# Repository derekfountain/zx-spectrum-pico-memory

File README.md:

# zx-spectrum-pico-memory

## A Microcontroller-based Lower Memory Implementation for the ZX Spectrum

This project replaces the 16K of lower memory in the ZX Spectrum with a Raspberry Pi Pico2. The RP2350
microcontoller on the Pico is programmed to emulate the original MK4116 DRAM ICs, and responds to reads
and writes from the Z80 CPU and the Spectrum's ULA support chip in the same way the original memory
does. It's not a cycle-perfect implementation, as I'll discuss, and to be honest it's of limited
practical use in this age of cheap SRAM based memory modules. But it was an interesting project, both
from a ZX point of view, and that of pushing the Pico to its limits.

### History

The original work on this project was done by myself and Andrew Menadue in 2022. Andrew designed the board
for the RP2040-based Raspberrry Pi Pico, and that work is still in
<a href="https://github.com/blackjetrock/zx-spectrum-pico-memory">his repository</a>. In late 2022 it
defeated us, the RP2040 just couldn't go fast enough to match 150ns silicon. I picked the project up
again in summer 2025 and had another look at it. Still unable to get it working, I changed it to use
the RP2350-based Pico2, and, that being a faster and more easily overclockable device, was able to
do the task. Just.

## The Technical Challenge

The MK4116 DRAM ICs in the ZX Spectrum provide the machine's lower 16K of RAM (memory locations 0x4000 to
0x7FFF inclusive). This memory area contains the memory used to create the Spectrum's memory mapped
video display (memory area 0x4000 to 0x5AFF inclusive). As such the 16K memory area is used by both the
Z80 CPU and the ULA support chip which is responsible for generating a video display from the memory
area.

The MK4116s used in the Spectrum are rated at 150ns, meaning a single read or write operation will
complete inside 150ns. Although the Z80 doesn't drive the DRAM ICs at their fastest speed, the ULA does.
This is because the ULA was tuned to generate the video image as quickly as possible, thereby not
slowing down the rest of the ZX Spectrum's system. The challenge with this DRAM emulator is to meet the
ULA's speed requirements, as opposed to the much more modest requirements of the Z80.

### Signal Patterns

The MK4116 was designed with a 7 bit address bus to meet physical space requirements and technical
limitations of the day, but to supply 16K of data it needs a 14 bit address bus. The solution to this
problem was to multiplex the address bus. The required 14 bits are sent from the Z80/ULA to the MK4116 in
two phases which make up a grid sort of pattern: the first 7 bits being supplied from the Z80/ULA as the "row"
and the second 7 bits being supplied from the Z80/ULA as the "column". Where the row and column intersect
in the internal MK4116 grid-like store, that's where the required data bit would be read from or written to.

The pattern for the MK4116 emulator to follow is therefore fairly simple: wait for the Row Address Strobe
(RAS) signal to appear, indicating the first 7 bits of the target address are on the address bus, then read
that value and store it. Then wait for the Column Address Strobe (CAS) signal to appear, indicating the
second 7 bits of the target address are on the address bus, then read that value and combine it with the
row value to get the full 14 bit address. Check the WRITE signal to see if the MK4116 should be doing a read
or write, and if it's a write go to the 8 bit data bus to fetch the value being written into the emulated
memory and write it into the Pico's onboard RAM. If the Z80/ULA is doing a read, go and fetch the data byte from
the Pico's onboard memory and put it on the data bus as an output. Once the Z80/ULA's done, go back to the top
and do it again.

The only real complication is that the MK4116 supports a "page mode" which the ULA (but not the Z80)
utilises. This is to support several reads in one go, and runs faster than the normal one-at-a-time mode.
In page mode, the RAS signal (and first 7 bits of the target addresses) are provided, and then the
repeated CAS signals (and associated second 7 bits of the target addresses) are provided one after the
other without ending the original RAS. It's a faster way of reading adjacent MK4116 memory and the ULA uses it to
build the video image as quickly as possible.

### Speed

The MK4116 may be a 1970s design, but it's still presented in silicon, which means it's fast. Not by today's
silicon standards maybe, but by todays CPU standards it is. The RP2040 natively runs at 133MHz, which means
one clock cycle is about 7.5 nanoseconds. The ARM chip runs approximately one instruction per clock cycle (it's
not quite that simple, but it's a rough approximation) which means it can run around 20 instructions in the
150ns access time of the original MK4116. So if the RP2040 was ever going to do everything required of it in
order to produce an accurate emulation, it was going to need to do it in very few instructions.

In pracise, 20 machine code instructions per transaction was never going to be enough to produce an emulation,
even of a simple storage device like the MK4116. Hefty overclocking was always going to be needed. Overclocking
to 270MHz might be fast enough.

It turned out that the RP2040-based Pico just wasn't fast enough. Back in 2022 when this project started I had
a particularly compliant one which overclocked to 360MHz, and that could run fast enough to satisfy the Z80's
requirements, but it was nowhere near fast enough to do the page mode reads the ULA needed. On this basis the
project stalled until 2025 when RP2350-based Pico2s became commonplace. All discussion and timings described
from this point onwards refer to the Pico2.

## Hardware

The hardware board was designed by Andrew Menadue. He did it based on the original Pico, the Pico2 not even
being discussed in 2022. It just fits inside the area of the Spectrum's PCB where the original MK4116s are
installed, and uses a handful of individual header pins to plug into the DRAM sockets.

On the top of the board is a voltage regulator and the Raspberry Pi Pico (the photo above doesn't have the
Pico installed). On the underside, inside the area between the Pico's pins,
are 3 level shifters which convert the Spectrum's +5V signals to the Pico's +3V3 voltage. Input signals from 
the Spectrum, like RAS, CAS and the 7 address lines go through level shifters set to a single direction. The
data bus needs to be reversible, so the Pico can both read and write data byte values. The level shifter
which controls the data bus therefore has a Pico-controllable direction toggle.

It's a 4 layer board, and is still a bit cramped. The current version is too tall when the Pico is installed
on it, preventing the Spectrum's keyboard being fitted back in place. If anyone ever has a practical use for
this device it'll probably need redesigning so as to allow the Spectrum to be reassembled. Consider the
current board to be a functioning prototype.

## Software, and the outstanding issue

The software was the main challenge with this project. When Andrew and I started we worked together, writing
code in C. When it started to hit limitations Andrew branched off and started trying to write parts of the
main loop in ARM assembly language. I stuck with C code. We both managed to produce code which would meet
the speed requirements of the Z80:

You can just about see the (C) 1982 message peering out from that mess.

But despite a lot of effort, neither of us produced code fast enough to make the Spectrum work properly and
the project stalled for 3 years.

When the Pico2 came out, with its faster cores and higher clock speed I picked up the project and had another
look. I added a few optimisatons, but generally the code I tried on the RP2350 was much the same as that which
was failing on the RP2040 3 years earlier. Only, on the RP2350, with a little more tuning, it worked. Just about.

You can see on there are a number of flickering arefacts on the screen. Those are caused by the DRAM emulator
not running quite fast enough to deliver page mode reads to the ULA. Each artefact is the result of a missed
read, the ULA finding essentially random data on its data bus.

The problem is shown on the oscilloscope capture. Yellow is RAS, and that can be seen to go low at the left
side. CAS, in light blue, goes low twice, then RAS goes high again. Those 2 CAS signals indicate 2 data bytes
being read by the ULA, one for pixel data, the other for colour data. That bit works fine. So RAS then goes
high, and then low again. Shortly after RAS goes low the second time (yellow line, centre of the image) CAS
goes high then low again. That's where the ULA is reading the pixel data for the second time, and that's
where the problem is. The gap between RAS going low, and CAS going low, is very tight, about 100ns. At that
point the code needs to spot that RAS has gone low, get the 7 bits of row address from the address bus, then
get back to the top of the loop quickly enough in order to spot that CAS has gone low again. Most times it
can manage it, but just occasionally it misses the CAS. That's when an artefact appears on screen.

So it's not quite good enough to use, and the software can't run any faster. PIOs might be an option to get
a bit more speed out of the emulator. Other than that we need to wait for Pico3. :)

[Derek Fountain](https://www.derekfountain.org/), September 2025

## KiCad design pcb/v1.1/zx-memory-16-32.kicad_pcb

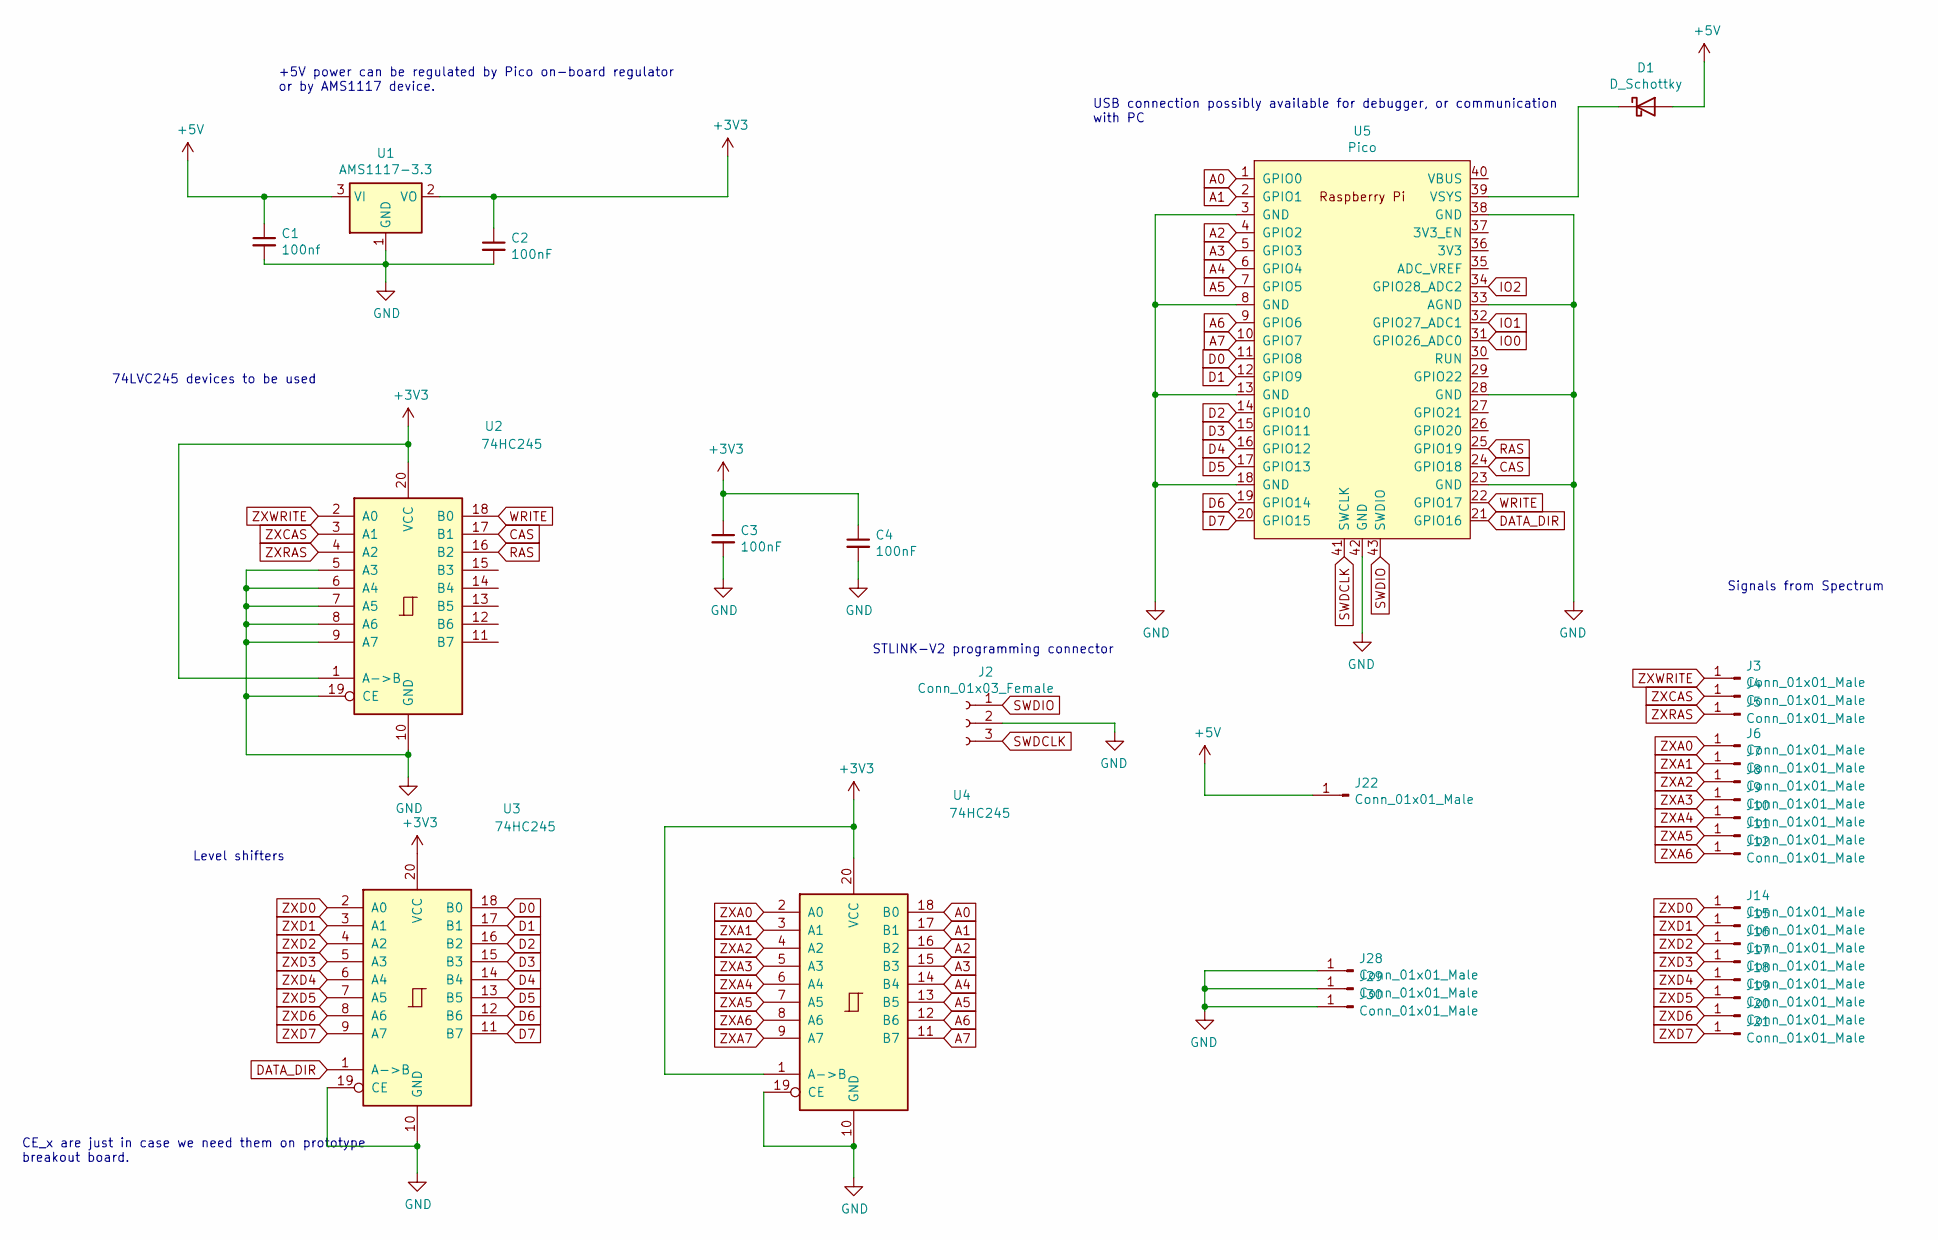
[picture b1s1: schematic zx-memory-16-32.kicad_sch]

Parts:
C1: 100nf; C_0805_2012Metric_Pad1.18x1.45mm_HandSolder
C2, C3, C4: 100nF; C_0805_2012Metric_Pad1.18x1.45mm_HandSolder
D1: D_Schottky; D_SOD-323_HandSoldering
J2: Conn_01x03_Female; PinHeader_1x03_P2.54mm_Vertical
J3, J4, J5, J6, J7, J8, J9, J10, J11, J12, J14, J15, J16, J17, J18, J19, J20, J21, J22, J28, J29, J30: Conn_01x01_Male; PinHeader_1x01_P2.00mm_Vertical
U1: AMS1117-3.3; SOT-223-3_TabPin2
U2, U3, U4: 74HC245; TSSOP-20_4.4x6.5mm_P0.65mm
U5: Pico; RPi_Pico_SMD_TH

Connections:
+3V3: C2.1, C3.1, C4.1, U1.2 (VO), U2.1 (A->B), U2.20 (VCC), U3.20 (VCC), U4.1 (A->B), U4.20 (VCC)
+5V: C1.1, D1.2 (A), J22.1, U1.3 (VI)
A0: U4.18 (B0), U5.1 (GPIO0)
A1: U4.17 (B1), U5.2 (GPIO1)
A2: U4.16 (B2), U5.4 (GPIO2)
A3: U4.15 (B3), U5.5 (GPIO3)
A4: U4.14 (B4), U5.6 (GPIO4)
A5: U4.13 (B5), U5.7 (GPIO5)
A6: U4.12 (B6), U5.9 (GPIO6)
A7: U4.11 (B7), U5.10 (GPIO7)
CAS: U2.17 (B1), U5.24 (GPIO18)
D0: U3.18 (B0), U5.11 (GPIO8)
D1: U3.17 (B1), U5.12 (GPIO9)
D2: U3.16 (B2), U5.14 (GPIO10)
D3: U3.15 (B3), U5.15 (GPIO11)
D4: U3.14 (B4), U5.16 (GPIO12)
D5: U3.13 (B5), U5.17 (GPIO13)
D6: U3.12 (B6), U5.19 (GPIO14)
D7: U3.11 (B7), U5.20 (GPIO15)
DATA_DIR: U3.1 (A->B), U5.21 (GPIO16)
GND: C1.2, C2.2, C3.2, C4.2, J2.2, J28.1, J29.1, J30.1, U1.1 (GND), U2.5 (A3), U2.6 (A4), U2.7 (A5), U2.8 (A6), U2.9 (A7), U2.10 (GND), U2.19 (CE), U3.10 (GND), U3.19 (CE), U4.10 (GND), U4.19 (CE), U5.3 (GND), U5.8 (GND), U5.13 (GND), U5.18 (GND), U5.23 (GND), U5.28 (GND), U5.33 (AGND), U5.38 (GND), U5.42 (GND)
IO0: U5.31 (GPIO26_ADC0)
IO1: U5.32 (GPIO27_ADC1)
IO2: U5.34 (GPIO28_ADC2)
unnamed: D1.1 (K), U5.39 (VSYS)
RAS: U2.16 (B2), U5.25 (GPIO19)
SWDCLK: J2.3, U5.41 (SWCLK)
SWDIO: J2.1, U5.43 (SWDIO)
WRITE: U2.18 (B0), U5.22 (GPIO17)
ZXA0: J6.1, U4.2 (A0)
ZXA1: J7.1, U4.3 (A1)
ZXA2: J8.1, U4.4 (A2)
ZXA3: J9.1, U4.5 (A3)
ZXA4: J10.1, U4.6 (A4)
ZXA5: J11.1, U4.7 (A5)
ZXA6: J12.1, U4.8 (A6)
ZXCAS: J4.1, U2.3 (A1)
ZXD0: J14.1, U3.2 (A0)
ZXD1: J15.1, U3.3 (A1)
ZXD2: J16.1, U3.4 (A2)
ZXD3: J17.1, U3.5 (A3)
ZXD4: J18.1, U3.6 (A4)
ZXD5: J19.1, U3.7 (A5)
ZXD6: J20.1, U3.8 (A6)
ZXD7: J21.1, U3.9 (A7)
ZXRAS: J5.1, U2.4 (A2)
ZXWRITE: J3.1, U2.2 (A0)

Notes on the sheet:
USB connection possibly available for debugger, or communication with PC
STLINK-V2 programming connector
Signals from Spectrum
+5V power can be regulated by Pico on-board regulator or by AMS1117 device.
CE_x are just in case we need them on prototype breakout board.
Level shifters
74LVC245 devices to be used

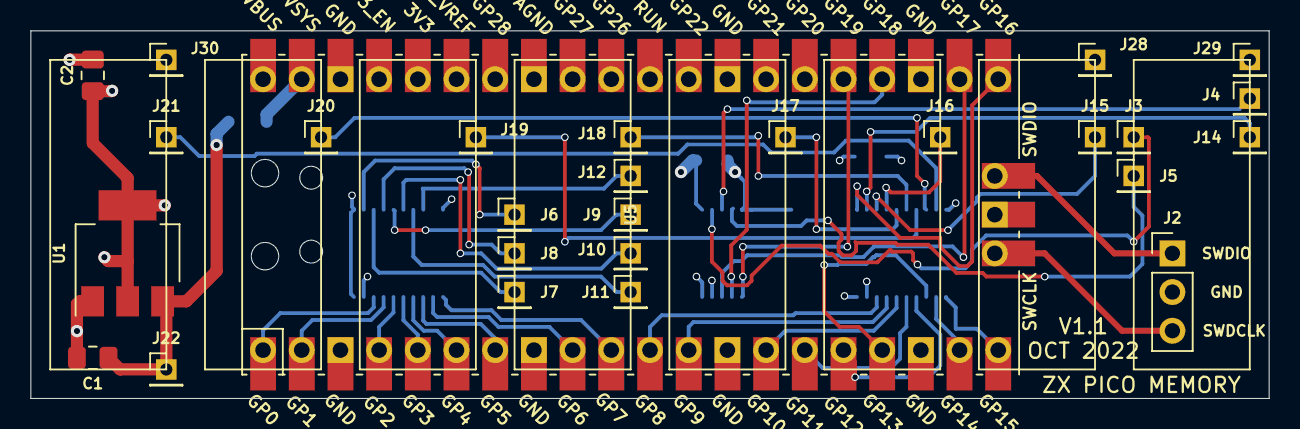
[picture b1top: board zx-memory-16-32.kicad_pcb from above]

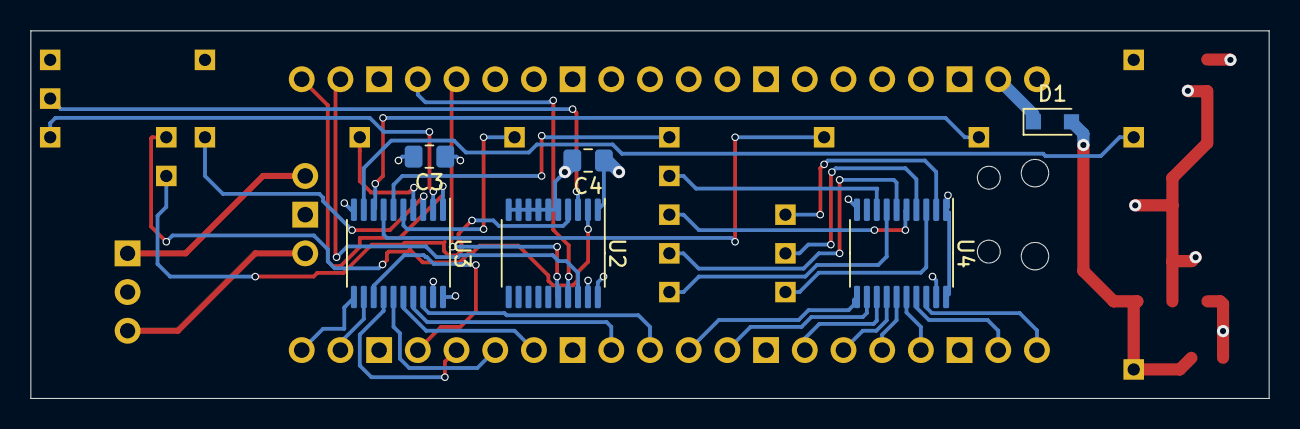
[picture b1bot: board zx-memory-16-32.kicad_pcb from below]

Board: 4 copper layers, 81.3 x 24.1 mm, 33 parts (6 on the bottom side), 44 nets.

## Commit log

2025-09-17 add datasheets
2025-09-17 add andrew's original PCB design, cleaned a bit and updated to latest kicad
2025-09-17 add the latest version of the firmware i have, no idea what state it's in
2025-09-19 remove redundant level shifter direction switching GPIOs
2025-09-19 remove redundant dbus pull downs
2025-09-19 remove redundant dbus drive strength configs
2025-09-19 remove redundant dbus slew rate configs
2025-09-19 remove redundant register keywords and the memory test pattern which never worked
2025-09-19 RAS related comments
2025-09-19 Indentation tidyup
2025-09-19 Comments and timings in the write path
2025-09-19 Working through the read path
2025-09-19 Replace the wait-for-CAS-to-go-low with a hardcoded NOP sled. Not sure this is useful
2025-09-20 Make the NOP sled into a macro, still not sure it's the way forward
2025-09-20 Remove redundant wait for CAS
2025-09-20 update to SDKv2, comments, the pico_sdk_import.cmake. no difference in functionality
2025-09-20 build on the Pico2 now working, device doesn't work for Z80 so that's a step backwards
2025-09-24 fix small bug in read path, still not working. going to try rp2040 again
2025-09-24 overclock rp2350 to 360MHz, z80 now happy, ula timings right, video contents wrong
2025-09-25 fix bug on page mode, z80 and ULA now working, quite a bit of video noise
2025-09-25 update all the timings comments
2025-09-25 small optimisation in the CAS path helps with the video corruptions a little
2025-09-25 another small optimisation in the CAS path helps with the video corruptions a little
2025-09-25 remove some unused code
2025-09-25 try writing into zx memory using the second core
2025-09-25 remove second core test code
2025-09-28 README work, couple of photos
2025-09-28 messy prompt photo
